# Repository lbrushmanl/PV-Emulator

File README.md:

# PV-Emulator
This project was to try and build a simple PV emulator. 

Images of test with my solar car buck converter (Buck setpoint is around 17V load was 3R3)

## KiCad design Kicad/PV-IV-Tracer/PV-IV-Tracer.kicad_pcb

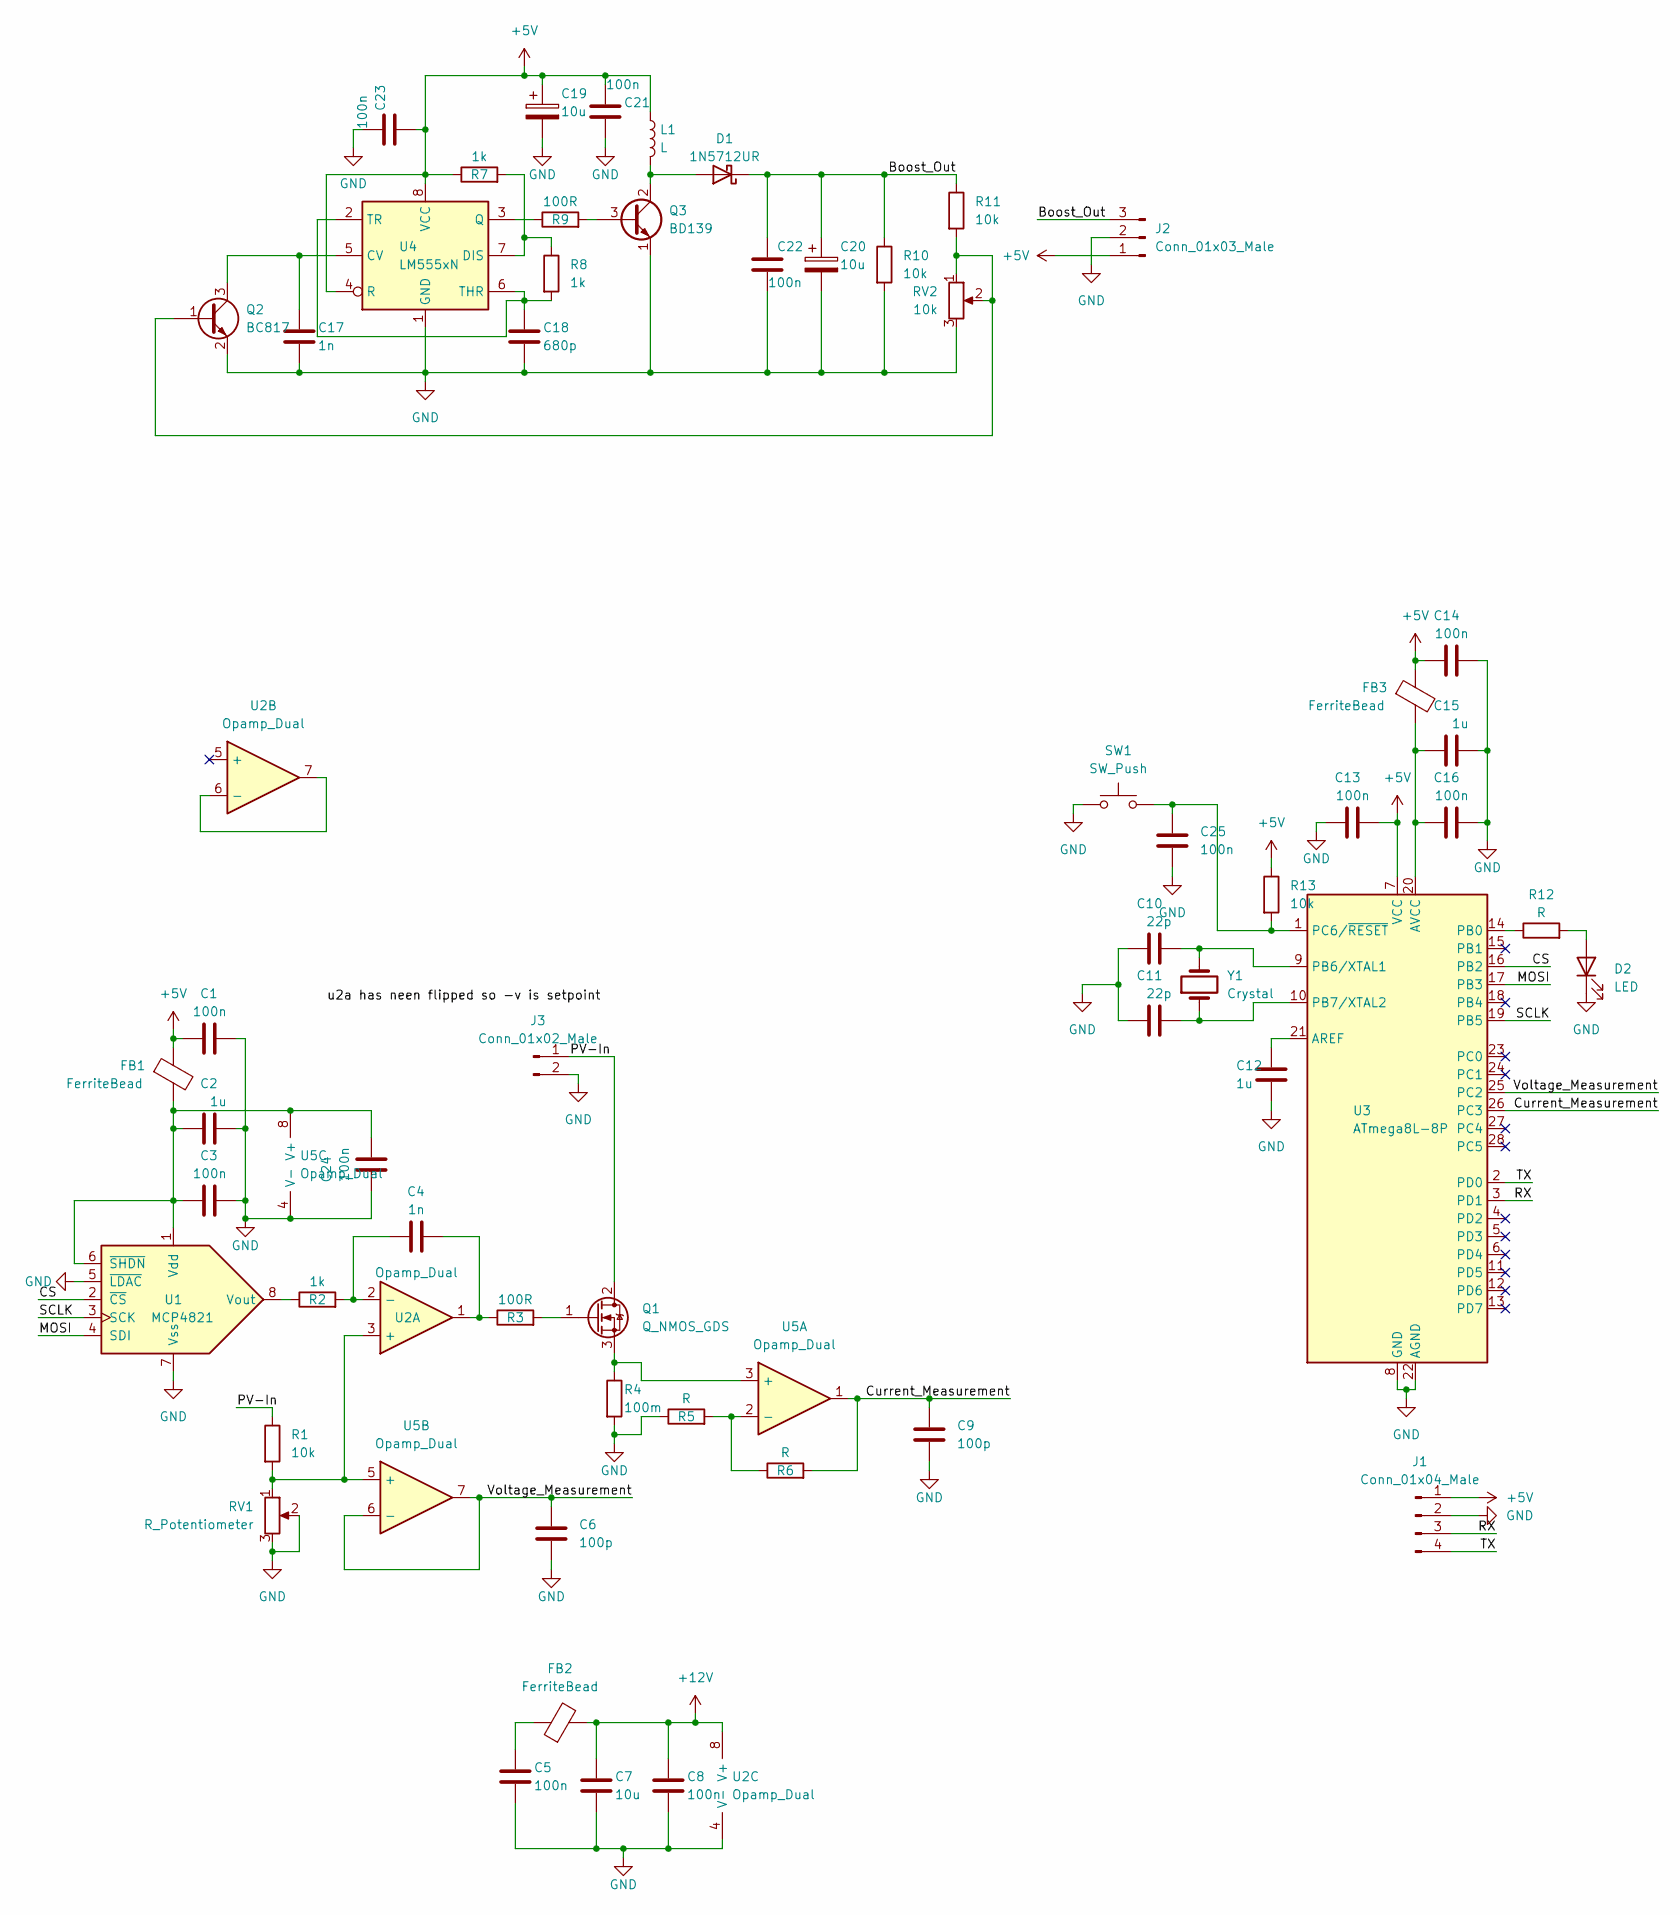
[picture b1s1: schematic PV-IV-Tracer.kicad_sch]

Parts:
C1, C3, C5, C8, C13, C14, C16, C21, C22, C23, C24, C25: 100n; C_0603_1608Metric_Pad1.08x0.95mm_HandSolder
C2, C12, C15: 1u; C_0805_2012Metric_Pad1.18x1.45mm_HandSolder
C4, C17: 1n; C_0603_1608Metric_Pad1.08x0.95mm_HandSolder
C6, C9: 100p; C_0603_1608Metric_Pad1.08x0.95mm_HandSolder
C7: 10u; C_0805_2012Metric_Pad1.18x1.45mm_HandSolder
C10, C11: 22p; C_0603_1608Metric_Pad1.08x0.95mm_HandSolder
C18: 680p; C_0603_1608Metric_Pad1.08x0.95mm_HandSolder
C19, C20: 10u; CP_Radial_D5.0mm_P2.00mm
D1: 1N5712UR; D_DO-15_P3.81mm_Vertical_KathodeUp
D2: LED; LED_D3.0mm
FB1, FB2, FB3: FerriteBead; R_1206_3216Metric_Pad1.30x1.75mm_HandSolder
J1: Conn_01x04_Male; PinHeader_1x04_P2.54mm_Vertical
J2: Conn_01x03_Male; PinHeader_1x03_P2.54mm_Horizontal
J3: Conn_01x02_Male; Molex_KK-396_5273-02A_1x02_P3.96mm_Vertical
L1: L; L_Radial_D6.0mm_P4.00mm
Q1: Q_NMOS_GDS; TO-247-3_Vertical
Q2: BC817; SOT-23
Q3: BD139; TO-126-3_Vertical
R1: 10k; R_Axial_DIN0207_L6.3mm_D2.5mm_P15.24mm_Horizontal
R2: 1k; R_1206_3216Metric_Pad1.30x1.75mm_HandSolder
R3: 100R; R_Axial_DIN0207_L6.3mm_D2.5mm_P15.24mm_Horizontal
R4: 100m; R_Axial_Power_L20.0mm_W6.4mm_P7.62mm_Vertical
R5, R6, R12: R; R_0603_1608Metric_Pad0.98x0.95mm_HandSolder
R7, R8: 1k; R_0603_1608Metric_Pad0.98x0.95mm_HandSolder
R9: 100R; R_1206_3216Metric_Pad1.30x1.75mm_HandSolder
R10, R11: 10k; R_0603_1608Metric_Pad0.98x0.95mm_HandSolder
R13: 10k; R_Axial_DIN0207_L6.3mm_D2.5mm_P10.16mm_Horizontal
RV1: R_Potentiometer; Potentiometer_Bourns_3296W_Vertical
RV2: 10k; Potentiometer_Bourns_3296W_Vertical
SW1: SW_Push
U1: MCP4821; SOIC-8-1EP_3.9x4.9mm_P1.27mm_EP2.29x3mm
U2, U5: Opamp_Dual; DIP-8_W7.62mm_LongPads
U3: ATmega8L-8P; DIP-28_W7.62mm_LongPads
U4: LM555xN; DIP-8_W7.62mm_LongPads
Y1: Crystal; Crystal_HC18-U_Vertical

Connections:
+5V: C1.1, C13.2, C14.1, C19.1, C21.1, C23.2, FB1.1, FB3.1, J1.1, J2.1, L1.1, R7.1, R13.1, U3.7 (VCC), U4.4 (R), U4.8 (VCC)
+12V: C7.1, C8.1, FB2.2, U2.8 (V+)
/Boost_Out: C20.1, C22.1, D1.1 (K), J2.3, R10.1, R11.1
/CS: U1.2 (~CS), U3.16 (PB2)
/Current_Measurement: C9.1, R6.2, U3.26 (PC3), U5.1
/MOSI: U1.4 (SDI), U3.17 (PB3)
/PV-In: J3.1, Q1.2 (D), R1.1
/RX: J1.3, U3.3 (PD1)
/SCLK: U1.3 (SCK), U3.19 (PB5)
/TX: J1.4, U3.2 (PD0)
/Voltage_Measurement: C6.1, U3.25 (PC2), U5.6 (-), U5.7
GND: C1.2, C2.2, C3.2, C5.2, C6.2, C7.2, C8.2, C9.2, C10.1, C11.1, C12.2, C13.1, C14.2, C15.2, C16.2, C17.2, C18.2, C19.2, C20.2, C21.2, C22.2, C23.1, C24.1, C25.2, D2.1 (K), J1.2, J2.2, J3.2, Q2.2 (E), Q3.1 (E), R4.2, R5.1, R10.2, RV1.2, RV1.3, RV2.3, SW1.1, U1.5 (~LDAC), U1.7 (Vss), U2.4 (V-), U3.8 (GND), U3.22 (AGND), U4.1 (GND), U5.4 (V-)
unnamed: C2.1, C3.1, C24.2, FB1.2, U1.1 (Vdd), U1.6 (~SHDN), U5.8 (V+)
unnamed: C4.1, R2.2, U2.2 (-)
unnamed: C4.2, R3.1, U2.1
unnamed: C5.1, FB2.1
unnamed: C10.2, U3.9 (PB6/XTAL1), Y1.2
unnamed: C11.2, U3.10 (PB7/XTAL2), Y1.1
unnamed: C12.1, U3.21 (AREF)
unnamed: C15.1, C16.1, FB3.2, U3.20 (AVCC)
unnamed: C17.1, Q2.3 (C), U4.5 (CV)
unnamed: C18.1, R8.2, U4.2 (TR), U4.6 (THR)
unnamed: C25.1, R13.2, SW1.2, U3.1 (PC6/~RESET)
unnamed: D1.2 (A), L1.2, Q3.2 (C)
unnamed: D2.2 (A), R12.2
unnamed: Q1.1 (G), R3.2
unnamed: Q1.3 (S), R4.1, U5.3 (+)
unnamed: Q2.1 (B), R11.2, RV2.1, RV2.2
unnamed: Q3.3 (B), R9.2
unnamed: R1.2, RV1.1, U2.3 (+), U5.5 (+)
unnamed: R2.1, U1.8 (Vout)
unnamed: R5.2, R6.1, U5.2 (-)
unnamed: R7.2, R8.1, U4.7 (DIS)
unnamed: R9.1, U4.3 (Q)
unnamed: R12.1, U3.14 (PB0)
unnamed: U2.6 (-), U2.7

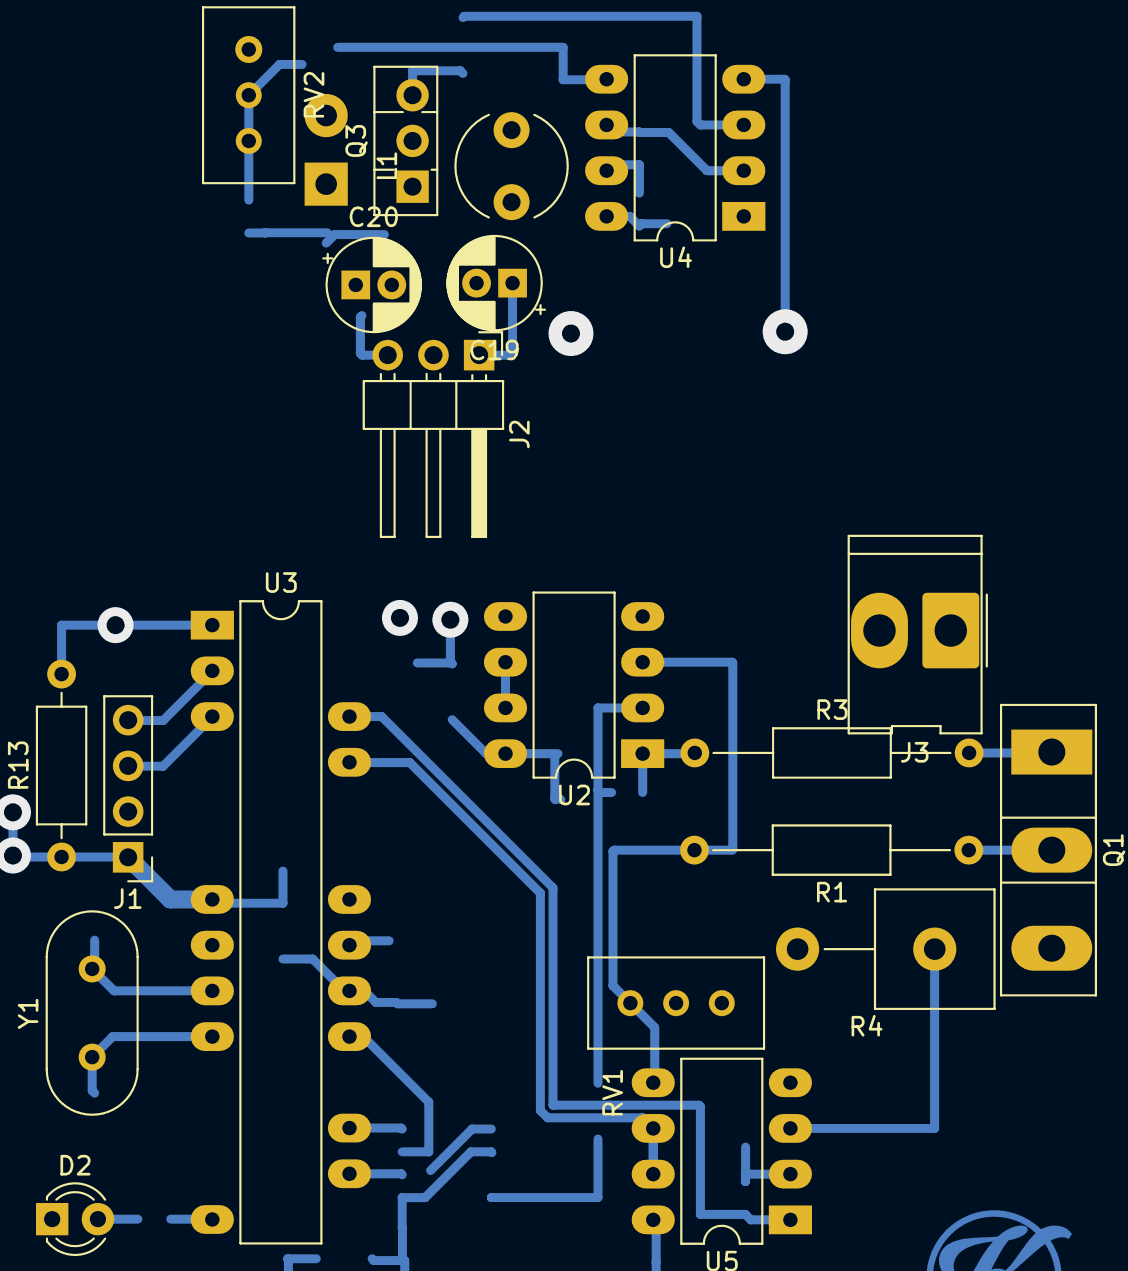
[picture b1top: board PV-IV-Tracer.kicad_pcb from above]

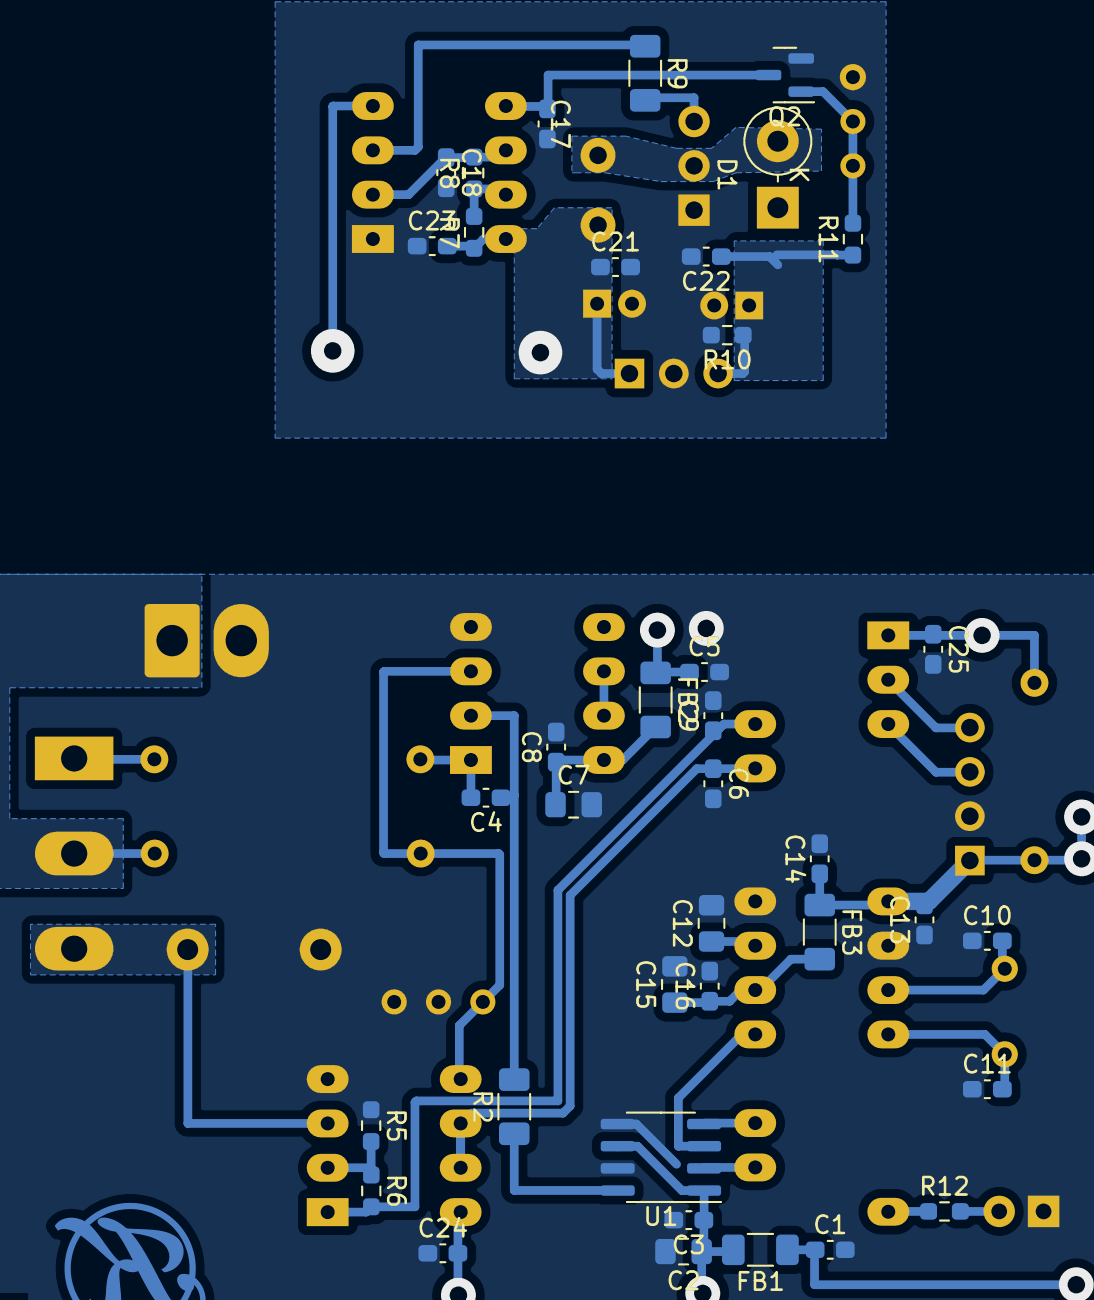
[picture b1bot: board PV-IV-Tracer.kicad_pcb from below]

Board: 2 copper layers, 58 parts (38 on the bottom side), 36 nets.

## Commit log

2023-02-16 Simulation files added and some code
2023-02-16 Pi Pico test code added for tracer and emulator
2023-02-16 Tracer Read me
2023-02-16 Added link to were I got the circuit for high side current sensing
2023-07-15 Added PCB and Schmatic
2023-07-15 V2 PCB swaped the opamp so that the inverting input is coneected to the setpoint changed PCB layout.
